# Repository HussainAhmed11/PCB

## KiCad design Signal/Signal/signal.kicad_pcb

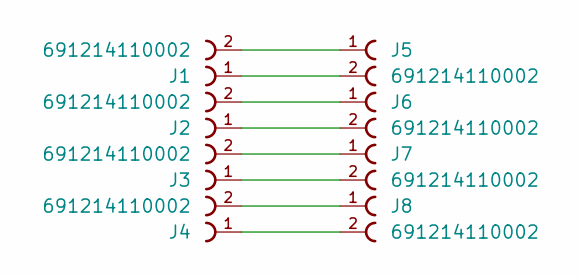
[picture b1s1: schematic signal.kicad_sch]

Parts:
J1, J2, J3, J4, J5, J6, J7, J8: 691214110002; Rosta 2

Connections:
unnamed: J1.1, J5.2
unnamed: J1.2, J5.1
unnamed: J2.1, J6.2
unnamed: J2.2, J6.1
unnamed: J3.1, J7.2
unnamed: J3.2, J7.1
unnamed: J4.1, J8.2
unnamed: J4.2, J8.1

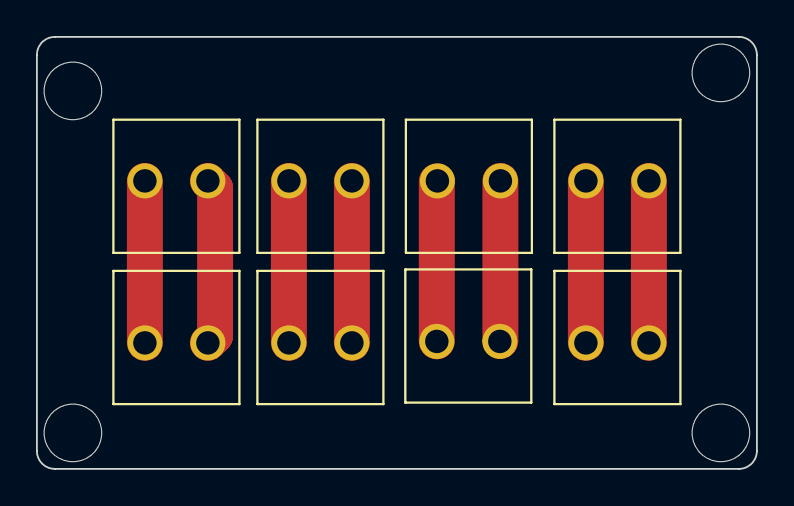
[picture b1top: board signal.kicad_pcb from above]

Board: 2 copper layers, 40.0 x 24.0 mm, 9 parts (1 on the bottom side), 8 nets.

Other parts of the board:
.: LOGO; OIROV

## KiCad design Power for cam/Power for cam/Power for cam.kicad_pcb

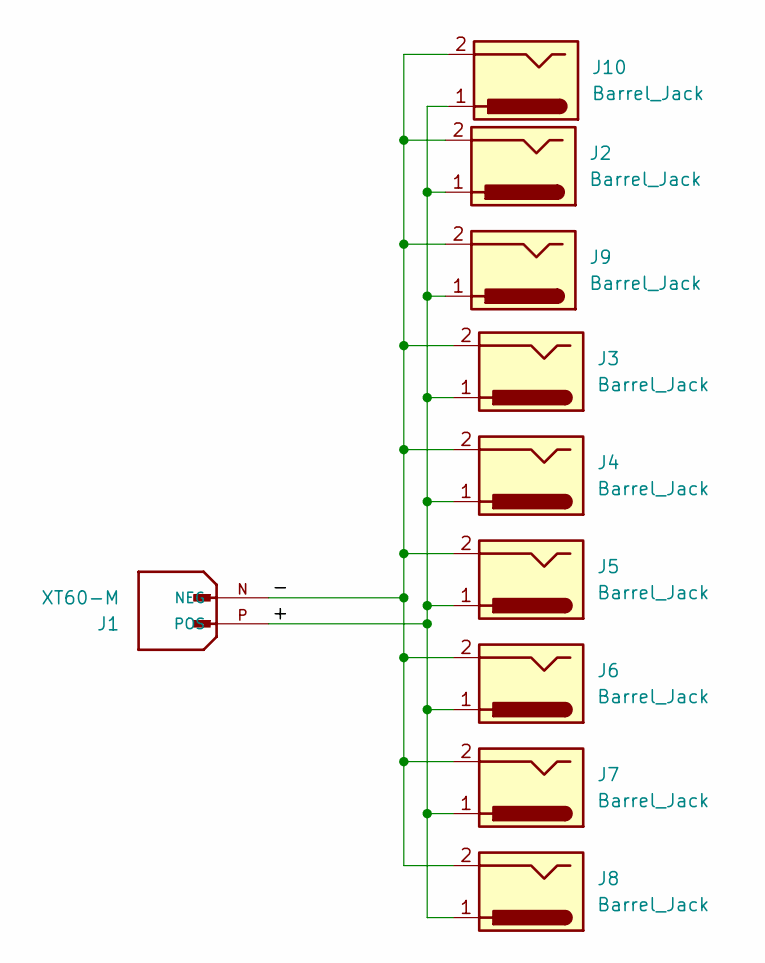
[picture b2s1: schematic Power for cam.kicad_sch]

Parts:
J1: XT60-M; AMASS_XT60-M; PARTREV V1.2
J2, J3, J4, J5, J6, J7, J8, J9, J10: Barrel_Jack; BarrelJack_CUI_PJ-063AH_Horizontal

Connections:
/+: J1.P (POS), J2.1, J3.1, J4.1, J5.1, J6.1, J7.1, J8.1, J9.1, J10.1; also elsewhere on the board
/-: J1.N (NEG), J2.2, J3.2, J4.2, J5.2, J6.2, J7.2, J8.2, J9.2, J10.2; also elsewhere on the board

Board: 2 copper layers, 11 parts (0 on the bottom side), 2 nets, no tracks yet.

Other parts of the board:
J5#2: Barrel_Jack; BarrelJack_CUI_PJ-063AH_Horizontal

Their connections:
/+: J5#2.1; also elsewhere on the board
/-: J5#2.2; also elsewhere on the board

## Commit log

2024-03-07 projects
2024-03-08 Mega Pro Pins Board
